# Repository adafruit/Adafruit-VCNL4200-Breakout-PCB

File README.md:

## Adafruit VCNL4200 Long Distance IR Proximity and Light Sensor - STEMMA QT / Qwiic PCB

<a href="http://www.adafruit.com/products/6064"><br/>
Click here to purchase one from the Adafruit shop</a>

PCB files for the Adafruit VCNL4200 Long Distance IR Proximity and Light Sensor - STEMMA QT / Qwiic. 

Format is EagleCAD schematic and board layout
* https://www.adafruit.com/product/6064

### Description

We've all been there. That thing is close but how close? When you need to measure a meter-or-so distance with reasonable accuracy, the VCNL4200 Long Distance Proximity Sensor from Vishay can do that for you. It's excellent for robotic or motion-detection situations. And. if perchance you also needed to measure the amount of light at the same time, you're in luck! The VCNL4200 can do that too, with it's built in ambient light sensor (ALS)

The VCNL4200 is a powerful two-in-one sensor, with a proximity sensor that works from 0 to 1.5m (59 inches) and light sensor with range of 0.003 to 1570 lux. It's the longest-range IR distance sensor we've seen other than the Sharp Analog distance sensors, and at a great price with I2C interface. Note that while the chip itself is specced for 1.5 meter distance measurements, that depends a bit on optimal lighting situations and high power configuration. We've found that 50-100cm is a good range to expect, and you won't get a lot of accuracy/precision as the detection object gets farther away. We normally suggest ToF sensors for long precision measurements, but sometimes you want the low cost and simplicity of infrared. Also, you get a 'free' light sensor which ToF sensors don't contain.

"OK, finally I can get started on my proximity and light sensing project, but how do I use it?" you say. To make life easier so you can focus on your important work, we've taken the VCNL4200 and put it onto a breakout PCB along with support circuitry to let you use this little wonder with 3.3V (Feather/Raspberry Pi) or 5V (Arduino/ Metro328) logic levels. Additionally since it speaks I2C you can easily connect it up with two wires (plus power and ground!).  We've even included SparkFun qwiic compatible STEMMA QT connectors for the I2C bus so you don't even need to solder! Just wire up to your favorite micro and you can use our CircuitPython/Python or Arduino drivers to easily interface with the VCNL4200 and make approximate approximations of proximity in no time! QT Cable is not included, but we have a variety in the shop. 

To give you some ability to tune your measurements for your situation, the VCNL4200 lets you adjust the integration time for both light sensing and proximity, IR LED power, duty cycle, multi-pulse, and sunlight-immunity. There's also interrupt output support for light or proximity measurement thresholds.

### License

Adafruit invests time and resources providing this open source design, please support Adafruit and open-source hardware by purchasing products from [Adafruit](https://www.adafruit.com)!

Designed by Limor Fried/Ladyada for Adafruit Industries.

Creative Commons Attribution/Share-Alike, all text above must be included in any redistribution. 
See license.txt for additional details.

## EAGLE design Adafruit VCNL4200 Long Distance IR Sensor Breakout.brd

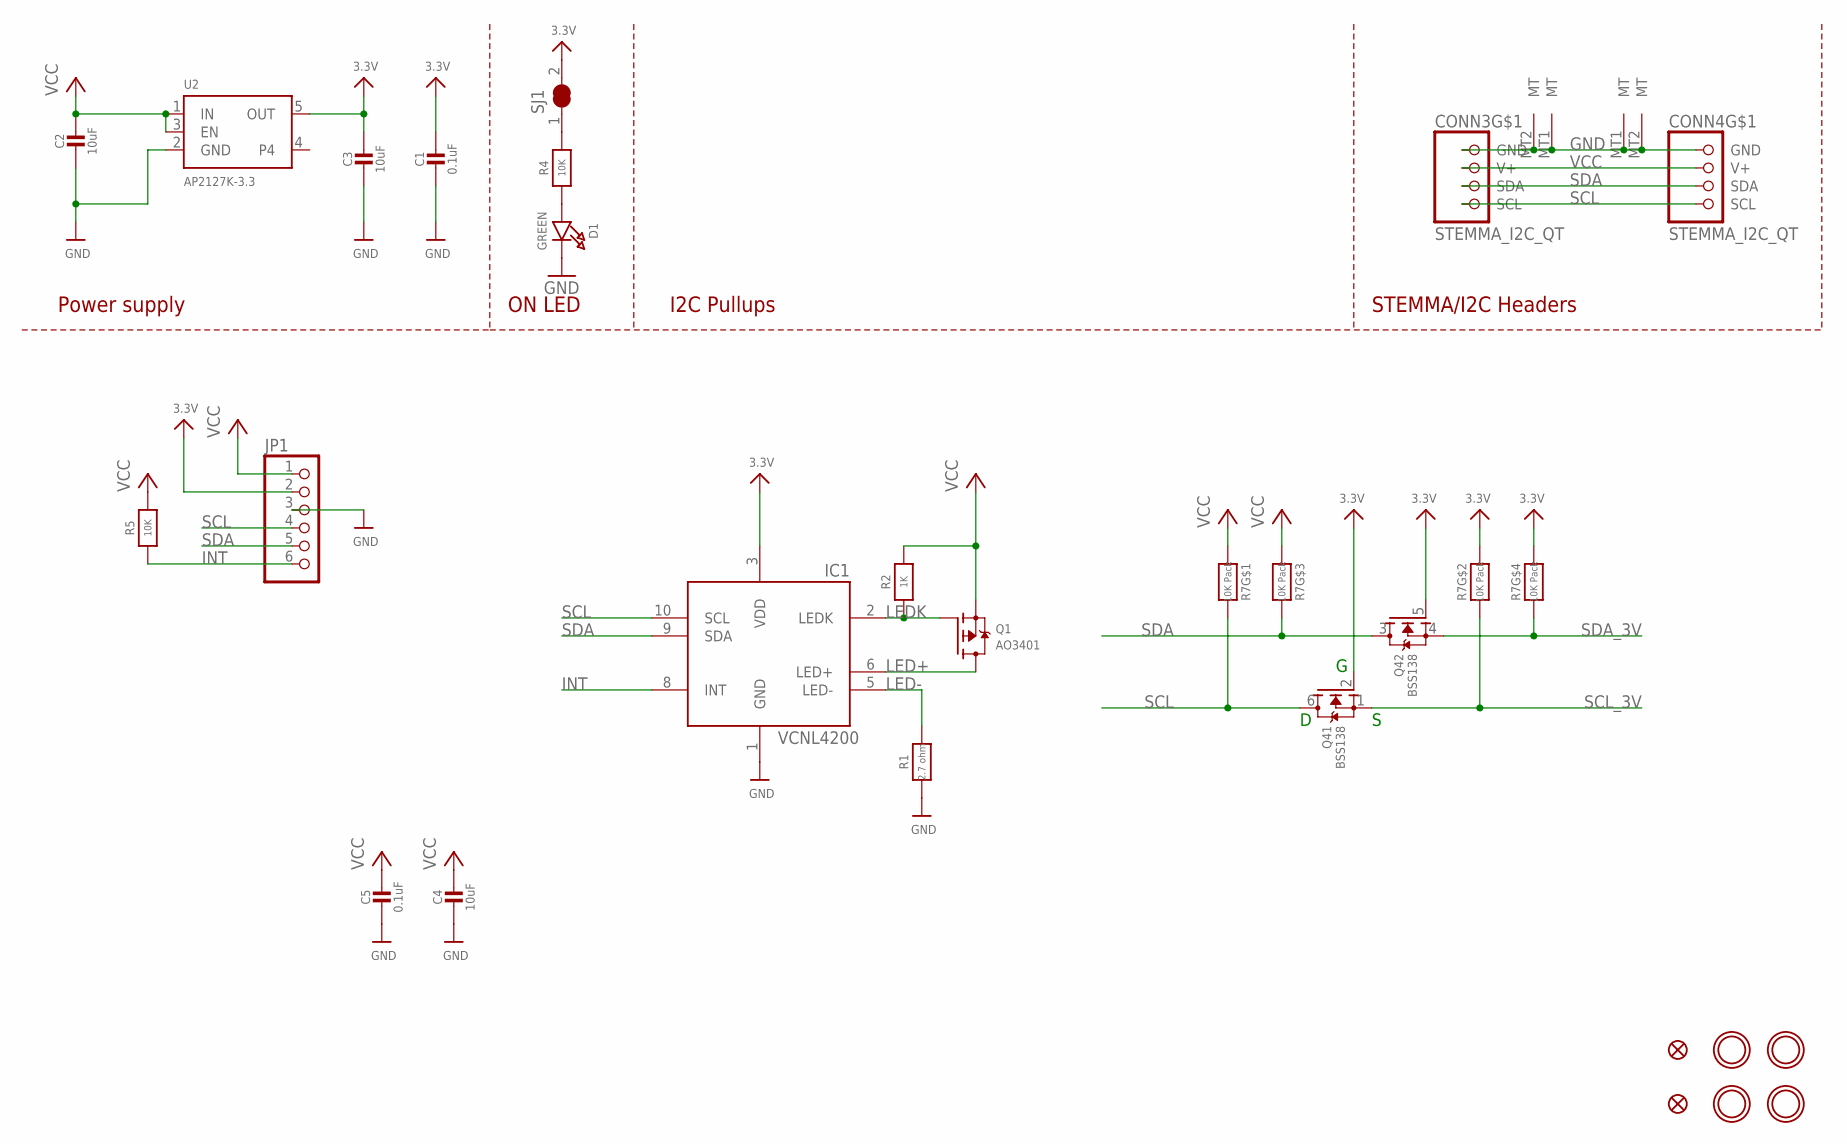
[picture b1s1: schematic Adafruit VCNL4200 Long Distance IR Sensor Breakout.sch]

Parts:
C1, C5: 0.1uF; 0603-NO
C2, C3, C4: 10uF; 0805-NO
CONN3, CONN4: STEMMA_I2C_QT; JST_SH4
D1: GREEN; CHIPLED_0603_NOOUTLINE
FID3, FID4: FIDUCIAL_1MM
IC1: VCNL4200
JP1: HEADER-1X670MIL; 1X06_ROUND_70
Q1: AO3401; SOT23-WIDE
Q4: BSS138; SOT363
R1: 2.7 ohm; 0603-NO
R2: 1K; 0603-NO
R4, R5: 10K; 0603-NO
R7: 10K Pack; RESPACK_4X0603
SJ1: SOLDERJUMPER_CLOSED; SOLDERJUMPER_CLOSEDWIRE
U2: AP2127K-3.3; SOT23-5
U$1, U$17, U$19, U$21: MOUNTINGHOLE2.5; MOUNTINGHOLE_2.5_PLATED

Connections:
3.3V: C1.1, C3.1, IC1.3 (VDD), JP1.2, Q4.2 (G), Q4.5 (G), R7.2 (1), R7.4 (1), SJ1.2, U2.5 (OUT)
GND: C1.2, C2.2, C3.2, C4.2, C5.2, CONN3.1 (GND), CONN3.MT1 (MT), CONN3.MT2 (MT), CONN4.1 (GND), CONN4.MT1 (MT), CONN4.MT2 (MT), D1.C, IC1.1 (GND), JP1.3, R1.1, U2.2 (GND)
INT: IC1.8 (INT), JP1.6, R5.1
LED+: IC1.6 (LED+), Q1.3 (D)
LED-: IC1.5 (LED-), R1.2
LEDK: IC1.2 (LEDK), Q1.1 (G), R2.1
unnamed: D1.A, R4.1
unnamed: R4.2, SJ1.1
SCL: CONN3.4 (SCL), CONN4.4 (SCL), IC1.10 (SCL), JP1.4, Q4.6 (D), R7.8 (2)
SCL_3V: Q4.1 (S), R7.7 (2)
SDA: CONN3.3 (SDA), CONN4.3 (SDA), IC1.9 (SDA), JP1.5, Q4.3 (D), R7.6 (2)
SDA_3V: Q4.4 (S), R7.5 (2)
VCC: C2.1, C4.1, C5.1, CONN3.2 (V+), CONN4.2 (V+), JP1.1, Q1.2 (S), R2.2, R5.2, R7.1, R7.3 (1), U2.1 (IN), U2.3 (EN)

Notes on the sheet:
I2C Pullups
STEMMA/I2C Headers
ON LED
Power supply

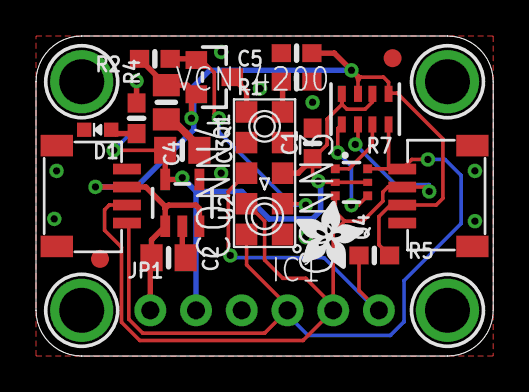
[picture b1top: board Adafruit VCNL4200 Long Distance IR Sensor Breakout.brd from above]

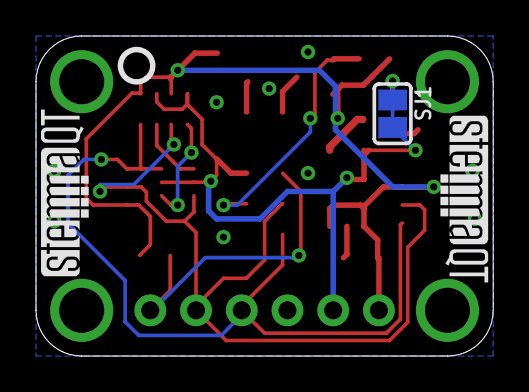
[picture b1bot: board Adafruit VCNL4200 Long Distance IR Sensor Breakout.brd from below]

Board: 2 copper layers, 25.4 x 17.8 mm, 40 parts (8 on the bottom side), 13 nets.

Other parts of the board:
PLABEL0: PLABEL0
PLABEL1: PLABEL1
PLABEL2: PLABEL2
PLABEL3: PLABEL3
PLABEL4: PLABEL4
PLABEL5: PLABEL5
PLABEL6: PLABEL6
PLABEL7: PLABEL7
PLABEL8: PLABEL8
PLABEL9: PLABEL9
PLABEL10: PLABEL10
U$22: ADAFRUIT_3.5MM
U$25: PCBFEAT-REV-040
U$30, U$31: STEMMAQT

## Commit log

2024-10-24 cookiecutter

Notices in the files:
parts and their libraries:
microbuilder: This work is placed in the public domain, and may be freely used for commercial and non-commercial work with the following conditions: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
